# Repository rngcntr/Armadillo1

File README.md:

# Armadillo1

It all started with a [Talk by ink](https://media.ccc.de/v/gpn22-498-tastaturen-ein-drama-mit-10-fingern) at GPN22, which inspired me to build my own customized wireless split keyboard. This one is fitted to the exact size of my hands and features a 36 key layout.

## Layout

I used [ergopad](https://pashutk.com/ergopad/) to determine the exact poitions of my fingertips that feel most comfortable. Then, I replicated the resulting layout manually using [ergogen](https://ergogen.ceoloide.com/).

## Keymap

For more details, see the [keymap README](keymap/README.md).

## Controller & Display

[nice!nano](https://nicekeyboards.com/nice-nano/) and [nice!view](https://nicekeyboards.com/nice-view).

## Switches

Kailh MX Jade. They're clicky switches with an above-average activation force.

## Keycaps

Smolo Keycaps from [BeeKeeb](https://shop.beekeeb.com/product/smolo-low-profile-keycap/).

## Risers

Self-printed. The design is available on [MakerWorld](https://makerworld.com/en/models/809248#profileId-750244).

## Case

Self-printed. I'm not yet fully satisfied by the design, so it's not yet published. If you're actually interested to print one yourself, please poke me.

## Stands

Two [MagSafe Stands](https://de.ugreen.com/products/45378?_pos=28&_sid=3c43091c2&_ss=r) by Ugreen.

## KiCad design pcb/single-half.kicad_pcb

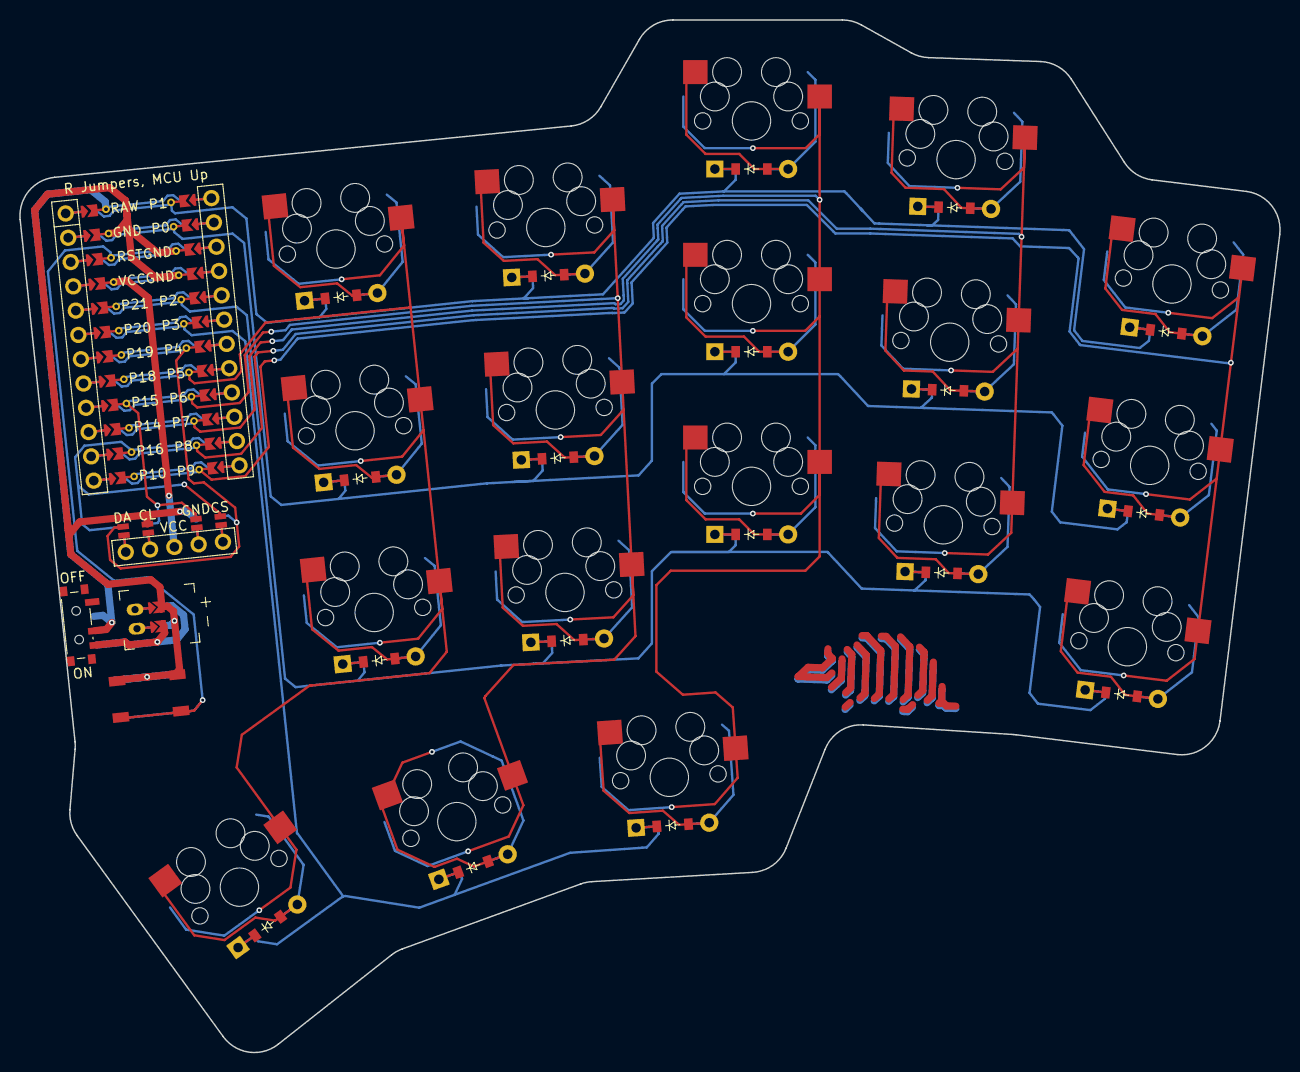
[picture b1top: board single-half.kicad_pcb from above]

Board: 2 copper layers, 131.0 x 107.4 mm, 40 parts (0 on the bottom side), 40 nets.

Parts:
D1, D2, D3, D4, D5, D6, D7, D8, D9, D10, D11, D12, D13, D14, D15, D16, D17, D18: ComboDiode
DISP1: display_nice_view
JST1: battery_connector_jst_ph_2
MCU1: mcu_nice_nano
PWR1: power_switch_smd_side
S1, S2, S3, S4, S5, S6, S7, S8, S9, S10, S11, S12, S13, S14, S15, S16, S17, S18: MX

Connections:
BAT_P: JST1.1, PWR1.1, PWR1.3
DISP1_1: DISP1.1, DISP1.10, DISP1.23
DISP1_2: DISP1.2, DISP1.11, DISP1.22
DISP1_4: DISP1.4, DISP1.12, DISP1.21
DISP1_5: DISP1.5, DISP1.13, DISP1.20
GND: DISP1.15, DISP1.25, JST1.2, MCU1.103, MCU1.104, MCU1.123
JST1_1: JST1.11, JST1.21, JST1.31
JST1_2: JST1.12, JST1.22, JST1.32
P0: D2.1, D5.1, D8.1, D11.1, D14.1, MCU1.102
P1: D3.1, D6.1, D9.1, D12.1, D15.1, MCU1.101
P2: D1.1, D4.1, D7.1, D10.1, D13.1, MCU1.105
P3: D16.1, D17.1, D18.1, MCU1.106
P4: DISP1.14, DISP1.24, MCU1.107
P5: MCU1.108, S1.1, S2.1, S3.1, S16.1
P6: MCU1.109, S4.1, S5.1, S6.1, S17.1
P7: MCU1.110, S7.1, S8.1, S9.1, S18.1
P8: MCU1.111, S10.1, S11.1, S12.1
P9: MCU1.112, S13.1, S14.1, S15.1
P15: DISP1.16, DISP1.26, MCU1.116
P16: DISP1.17, DISP1.27, MCU1.114
RAW: MCU1.124, PWR1.2
VCC: DISP1.3, MCU1.121
index_bottom: D4.2, S4.2
index_home: D5.2, S5.2
index_top: D6.2, S6.2
inner_bottom: D1.2, S1.2
inner_home: D2.2, S2.2
inner_top: D3.2, S3.2
layer_cluster: D17.2, S17.2
middle_bottom: D7.2, S7.2
middle_home: D8.2, S8.2
middle_top: D9.2, S9.2
mod_cluster: D18.2, S18.2
pinky_bottom: D13.2, S13.2
pinky_home: D14.2, S14.2
pinky_top: D15.2, S15.2
ring_bottom: D10.2, S10.2
ring_home: D11.2, S11.2
ring_top: D12.2, S12.2
space_cluster: D16.2, S16.2

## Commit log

2024-12-29 Add controller info
